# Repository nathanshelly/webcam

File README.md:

# Webcam

*Built by Jacob Bruce and Nathan Shelly*

## Description

This project aims to walk through the steps of designing and building a webcam from scratch. We'll walk through PCB (printed circuit board) design, soldering of components, 3D printing of the outer enclosure, MCU code and website code to enable you to make your own webcam, or modify our design however you'd like! This repository acts as the landng page to various parts of the project. Here we'll have various files such as our PCB designs, our CAD files and a bill of materials. Our [microcontroller code](https://github.com/nathanshelly/webcam_mcu_code) and [server code](https://github.com/nathanshelly/webcam_web_code) each have their own repositories, where our full code for each can be explored or downloaded. If you have any interest in duplicating or extending the project, please contact the authors - we'd be happy to help out in any way we can.

3D Printed Enclosure             |  Wood Milled Enclosure
:-------------------------:|:-------------------------:
  |  

## Assembly order

We recommend the following order to assemble this open-source project from scratch.

1. [Order components](#order-all-components)
2. [Solder board](#solder-components-onto-board)
3. [Configure wifi](#configure-wifi-chip)
4. [Configure MCU](#configure-microcontroller)
5. [Configure server](#configure-server)
6. [Print enclosure](#print-enclosure)

## Thanks

A big thank you to our instructor, Professor Ilya Mikhelson of Northwestern University. This webcam project was created as a part of his Engineering System Design sequence.

## Order components

We've included a [Bill of Materials](./BOM.txt) that details all of the components used in the project - primarily components to be soldered onto the board, but also some cabling to connect to it.

Here are some potential places to order from: [Mouser](http://www.mouser.com/), [Digikey](https://www.digikey.com/), [Robotshop](http://www.robotshop.com/).

You'll also need to order the PCB to solder the components onto. We've included our [raw EAGLE files](./board/), as well as a set of [Gerber files](./board/gerber_files.zip) that can be sent directly to the manufacturer.

## Solder board

If you have experience with surface mount soldering, this should be fairly straightforward. If you do not, we recommend practicing some before working with any expensive components. [This playlist](https://www.youtube.com/playlist?list=PL1ec5YBm_crySPZat6Y5e9hxfIUI7d97B) has many useful videos for this project, including several specifically on soldering.

We recommend the following soldering order to unit test each component before moving forward.

1. Power circuit: barrel jack, voltage regulator, power indicator LED, associated resistors and capacitors. Confirm that ground and power are not connected via continuity test. Plug in power cord and confirm that the power indicator lights up.

2. Microcontroller, PLL circuit, crystal oscillator, buttons, associated bypass capacitors, and header pins. After soldering the MCU, confirm each connection via continuity test to another via or pad, and confirm that no pins are connected to power or ground that shouldn't be. Connect the Atmel debugger, power the circuit, and confirm that the device signature can be read from Atmel Studio.

3. Wifi Chip, indicator LEDs, header pins, and associated bypass capacitors. Again, confirm each connection individually before proceeding. To confirm proper operation, perform step 4 to configure the chip.

4. Microphone and associated passive components.

5. Camera module and associated passive components. Be sure to solder the connector without the module inserted, and again confirm connections individually before proceeding.

## Configure wifi chip

The wifi chip requires a fair degree of configuration to work correctly. Zentri helpfully includes an OS to which commands are issued, and it's quite easy to work with their [command API](https://docs.zentri.com/zentrios/wz/3.3/cmd/commands). We recommend issuing these commands via a terminal emulator ([TeraTerm](https://ttssh2.osdn.jp/index.html.en) for windows or [CoolTerm](http://freeware.the-meiers.org/) for Mac) connected to the header pins for the UART communication via an FTDI cable. If you use the FTDI cable, make sure that the microcontroller will not be attempting to use the UART bus (either because no code has been loaded onto it or because it does not configure or use its UART module), or bus contention will result. These operations can also be performed by editing the MCU code and running commands, but that's much more difficult and harder to read/interpret feedback.

1. Connect to the chip. Confirm your connection by hitting Enter; the chip should respond with Ready.
2. If you're using a network which requires registration, obtain its mac address via the get wl m query, and register it to the network.
3. Connect the device to your network with the setup command. Once the command has been run, find the device's network on your computer. Connect to it, visit setup.com, and follow the prompts to connect to the desired network. Thereafter, the web console can be accessed from `http://zentrios-XYZ.local/`, where XYZ are the last 3 digits of your wifi chip's serial number.
4. Register with Zentri, and claim your device via the dms claim command.
5. Update the device's firmware with the OTA command.
6. Set the indicator GPIOs to indicate on the correct LEDs by running the following commands:

```
set sy i g wlan 20
set sy i g network 21
set sy i g softap 22
```

7. (Do this step only if you want to serve over HTTPS) Load TLS certificate onto the chip using its file uploader. Change its default TLS certificate to this file via the ne t a command.

8. Change the baud rate by setting the ua b variable for UART1. The default speed for UART1 is 115200, and our system is designed to run at 2.5Mbauds. You may want to turn the baud rate down in the MCU code to test operation before turning both up to this high speed - we haven't found a terminal emulator that can successfully interpret messages at this speed, and any issues can be difficult to debug.

## Configure microcontroller

To load our MCU code (found in [this separate repository](https://github.com/nathanshelly/webcam_mcu_code)) onto the microcontroller, first connect your Atmel debugger to the corresponding header pins and to your computer. Open our Atmel project, and connect to the debugger. Compile and load the code - it should run correctly now that the wifi chip is properly configured.

## Configure server

Our back-end stack consists of NGINX and Tornado on a Google Compute Engine instance. This could be hosted on any cloud provider or personal server. NGNIX directly handles requests for our static HTML, CSS and Javascript files while serving as a reverse proxy forwarding dynamic websocket requests to our Tornado server. We currently serve the website over HTTPS though this is not strictly necessary. If you plan to also serve over HTTPS our [NGINX configuration file](./nginx_config) would require only changing the server name in the port 80 and 443 blocks and then updating the ssl_certificate/key lines to point to your certificate. If you've never served over HTTPS before but would like to try we highly recommend getting a certificate from [LetsEncrypt](https://letsencrypt.org/) (they have great documentation and are free!).

If you want to serve over HTTP instead you'll need to move the location directives from the 443 block to the 80 block and remove the `return 301 https://$server_name$request_uri;` line which redirects all HTTP traffic to HTTPS. The ssl_certificate/key lines can also be removed.

The static files and our Tornado server file are all hosted in [this repository](https://github.com/nathanshelly/webcam_web_code) along with a more in-depth description of setting up the website.

## Print enclosure

For designing the enclosure we used an online program called [Onshape](https://www.onshape.com/). This provides a convenient way to edit CAD files with low overhead though it lacks some functionality from a fuller editor like Solidworks. View our [Onshape project here](https://cad.onshape.com/documents/ae298fb239b6988d4ccff146/w/2fbac33a8452420bf0238e8e/e/6b2309d9b32e628505d094b1).

We've also provided the raw files in two different formats. If you'd like to modify our design [here](./enclosure/editable) are .sldprt files. If you'd like to print our design as is [here](./enclosure/printable) are .stl files.

## Enjoy!

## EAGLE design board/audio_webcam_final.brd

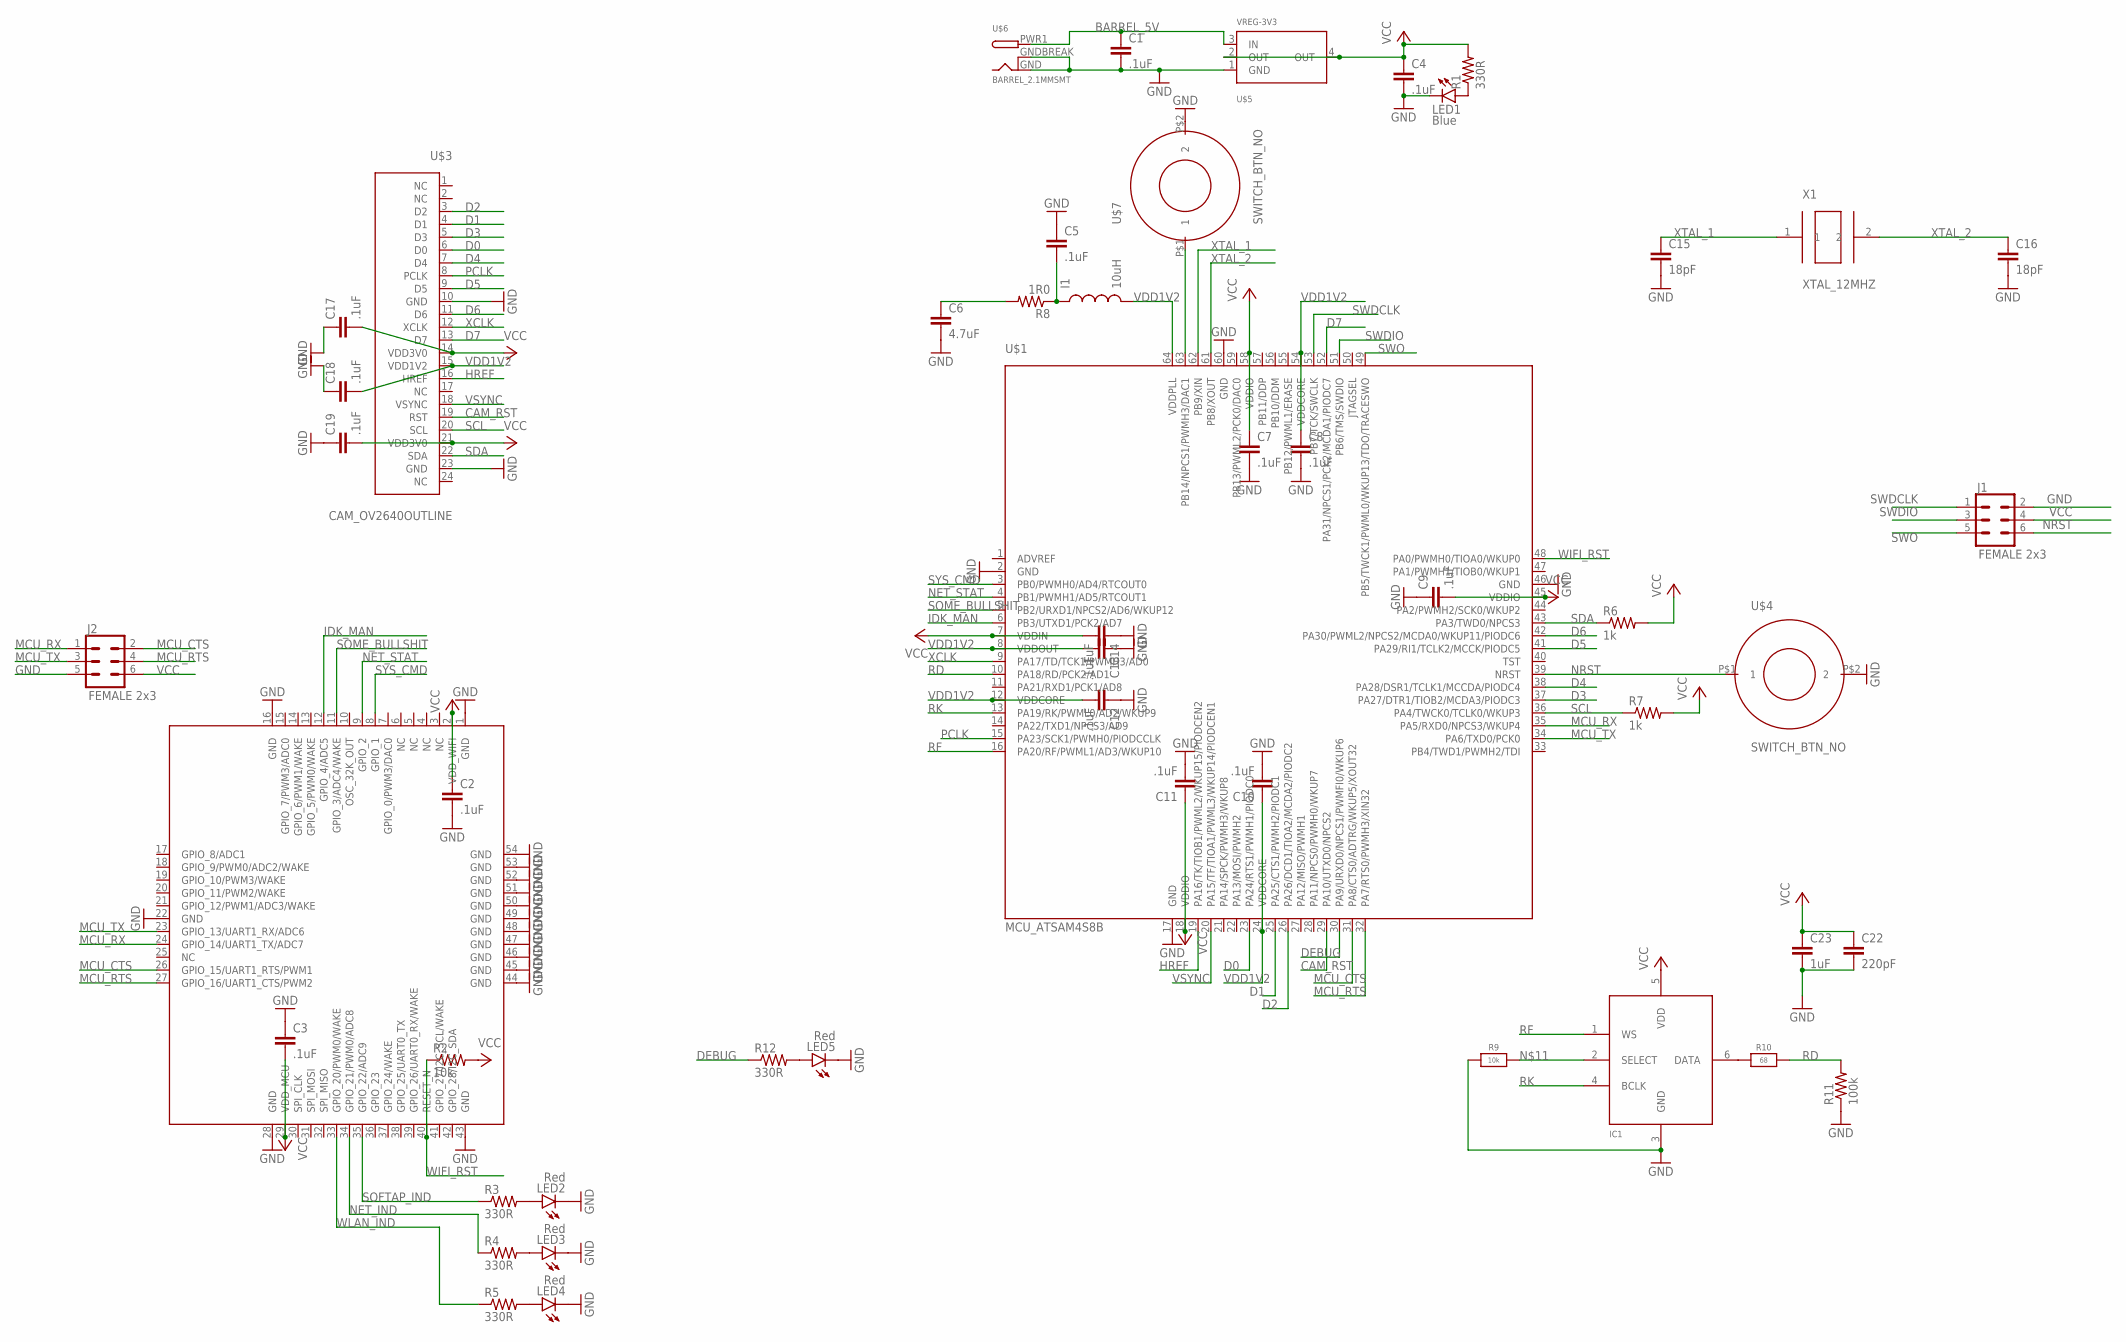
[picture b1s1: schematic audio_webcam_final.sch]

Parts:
C1, C2, C3, C4, C5, C7, C8, C9, C10, C11, C12, C13, C14, C17, C18, C19: .1uF; 0805
C6: 4.7uF; 0805
C15, C16: 18pF; 0805
C22: 220pF; 0805
C23: 1uF; 0805
I1: 10uH; 0805
IC1: MIC_I2S_SPH0645; SPH0645LM4H
J1, J2: FEMALE 2x3; 2X3
LED1: Blue; LED-0603
LED2, LED3, LED4, LED5: Red; LED-0603
R1, R3, R4, R5, R12: 330R; 0805
R2: 10k; 0805
R6, R7: 1k; 0805
R8: 1R0; 0805
R9: 10k; 0603-NO
R10: 68; 0603-NO
R11: 100k; 0805
U$1: MCU_ATSAM4S8B; QFP50P1200X1200X160-64N
U$2: WIFI_AMW004; AMW004
U$3: CAM_OV2640OUTLINE; CAM_CONN
U$4, U$7: SWITCH_BTN_NO; BTN_2
U$5: VREG-3V3; R-PDSO-G4_TI
U$6: BARREL_2.1MMSMT; DCJACK_2MM_SMT
X1: XTAL_12MHZ; ABM7-16.000MHZ-D2Y-T

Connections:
BARREL_5V: C1.1, U$5.3 (IN), U$6.PWR1 (PWR)
CAM_RST: U$1.29 (PA10/UTXD0/NPCS2), U$3.19 (RST)
D0: U$1.23 (PA24/RTS1/PWMH1/PIODC0), U$3.6 (D0)
D1: U$1.25 (PA25/CTS1/PWMH2/PIODC1), U$3.4 (D1)
D2: U$1.26 (PA26/DCD1/TIOA2/MCDA2/PIODC2), U$3.3 (D2)
D3: U$1.37 (PA27/DTR1/TIOB2/MCDA3/PIODC3), U$3.5 (D3)
D4: U$1.38 (PA28/DSR1/TCLK1/MCCDA/PIODC4), U$3.7 (D4)
D5: U$1.41 (PA29/RI1/TCLK2/MCCK/PIODC5), U$3.9 (D5)
D6: U$1.42 (PA30/PWML2/NPCS2/MCDA0/WKUP11/PIODC6), U$3.11 (D6)
D7: U$1.52 (PA31/NPCS1/PCK2/MCDA1/PIODC7), U$3.13 (D7)
DEBUG: R12.1, U$1.30 (PA9/URXD0/NPCS1/PWMFI0/WKUP6)
GND: C1.2, C2.2, C3.1, C4.2, C5.1, C6.2, C7.2, C8.2, C9.1, C10.2, C11.2, C12.1, C13.1, C14.1, C15.2, C16.2, C17.1, C18.1, C19.1, C22.2, C23.2, IC1.3 (GND), J1.2, J2.5, LED1.C, LED2.C, LED3.C, LED4.C, LED5.C, R9.1, R11.1, U$1.2 (GND), U$1.17 (GND), U$1.46 (GND), U$1.60 (GND), U$2.1 (GND), U$2.16 (GND), U$2.22 (GND), U$2.28 (GND), U$2.43 (GND), U$2.44 (GND), U$2.45 (GND), U$2.46 (GND), U$2.47 (GND), U$2.48 (GND), U$2.49 (GND), U$2.50 (GND), U$2.51 (GND), U$2.52 (GND), U$2.53 (GND), U$2.54 (GND), U$3.10 (GND), U$3.23 (GND), U$4.P$2 (2), U$5.1 (GND), U$6.GND, U$6.GNDBREAK, U$7.P$2 (2)
HREF: U$1.19 (PA16/TK/TIOB1/PWML2/WKUP15/PIODCEN2), U$3.16 (HREF)
IDK_MAN: U$1.6 (PB3/UTXD1/PCK2/AD7), U$2.12 (GPIO_4/ADC5)
MCU_CTS: J2.2, U$1.31 (PA8/CTS0/ADTRG/WKUP5/XOUT32), U$2.26 (GPIO_15/UART1_RTS/PWM1)
MCU_RTS: J2.4, U$1.32 (PA7/RTS0/PWMH3/XIN32), U$2.27 (GPIO_16/UART1_CTS/PWM2)
MCU_RX: J2.1, U$1.35 (PA5/RXD0/NPCS3/WKUP4), U$2.24 (GPIO_14/UART1_TX/ADC7)
MCU_TX: J2.3, U$1.34 (PA6/TXD0/PCK0), U$2.23 (GPIO_13/UART1_RX/ADC6)
unnamed: LED2.A, R3.2
unnamed: LED3.A, R4.2
unnamed: LED4.A, R5.2
unnamed: C5.2, I1.1, R8.1
unnamed: C6.1, R8.2
unnamed: LED1.A, R1.1
unnamed: U$1.63 (PB14/NPCS1/PWMH3/DAC1), U$7.P$1 (1)
unnamed: LED5.A, R12.2
unnamed: IC1.2 (SELECT), R9.2
unnamed: IC1.6 (DATA), R10.1
NET_IND: R4.1, U$2.34 (GPIO_21/PWM0/ADC8)
NET_STAT: U$1.4 (PB1/PWMH1/AD5/RTCOUT1), U$2.9 (GPIO_2)
NRST: J1.6, U$1.39 (NRST), U$4.P$1 (1)
PCLK: U$1.15 (PA23/SCK1/PWMH0/PIODCCLK), U$3.8 (PCLK)
RD: R10.2, R11.2, U$1.10 (PA18/RD/PCK2/AD1)
RF: IC1.1 (WS), U$1.16 (PA20/RF/PWML1/AD3/WKUP10)
RK: IC1.4 (BCLK), U$1.13 (PA19/RK/PWML0/AD2/WKUP9)
SCL: R7.1, U$1.36 (PA4/TWCK0/TCLK0/WKUP3), U$3.20 (SCL)
SDA: R6.1, U$1.43 (PA3/TWD0/NPCS3), U$3.22 (SDA)
SOFTAP_IND: R3.1, U$2.35 (GPIO_22/ADC9)
SOME_BULLSHIT: U$1.5 (PB2/URXD1/NPCS2/AD6/WKUP12), U$2.11 (GPIO_3/ADC4/WAKE)
SWDCLK: J1.1, U$1.53 (PB7/TCK/SWCLK)
SWDIO: J1.3, U$1.51 (PB6/TMS/SWDIO)
SWO: J1.5, U$1.49 (PB5/TWCK1/PWML0/WKUP13/TDO/TRACESWO)
SYS_CMD: U$1.3 (PB0/PWMH0/AD4/RTCOUT0), U$2.8 (GPIO_1)
VCC: C2.1, C3.2, C4.1, C7.1, C9.2, C11.1, C14.2, C17.2, C19.2, C22.1, C23.1, IC1.5 (VDD), J1.4, J2.6, R1.2, R2.2, R6.2, R7.2, U$1.7 (VDDIN), U$1.18 (VDDIO), U$1.45 (VDDIO), U$1.58 (VDDIO), U$2.2 (VDD_WIFI), U$2.29 (VDD_MCU), U$3.14 (VDD3V0), U$3.21 (VDD3V0), U$5.2 (OUT), U$5.4 (OUT)
VDD1V2: C8.1, C10.1, C12.2, C13.2, C18.2, I1.2, U$1.8 (VDDOUT), U$1.12 (VDDCORE), U$1.24 (VDDCORE), U$1.54 (VDDCORE), U$1.64 (VDDPLL), U$3.15 (VDD1V2)
VSYNC: U$1.20 (PA15/TF/TIOA1/PWML3/WKUP14/PIODCEN1), U$3.18 (VSYNC)
WIFI_RST: R2.1, U$1.48 (PA0/PWMH0/TIOA0/WKUP0), U$2.40 (RESET_N)
WLAN_IND: R5.1, U$2.33 (GPIO_20/PWM0/WAKE)
XCLK: U$1.9 (PA17/TD/TCK1/PWMH3/AD0), U$3.12 (XCLK)
XTAL_1: C15.1, U$1.62 (PB9/XIN), X1.1
XTAL_2: C16.1, U$1.61 (PB8/XOUT), X1.2

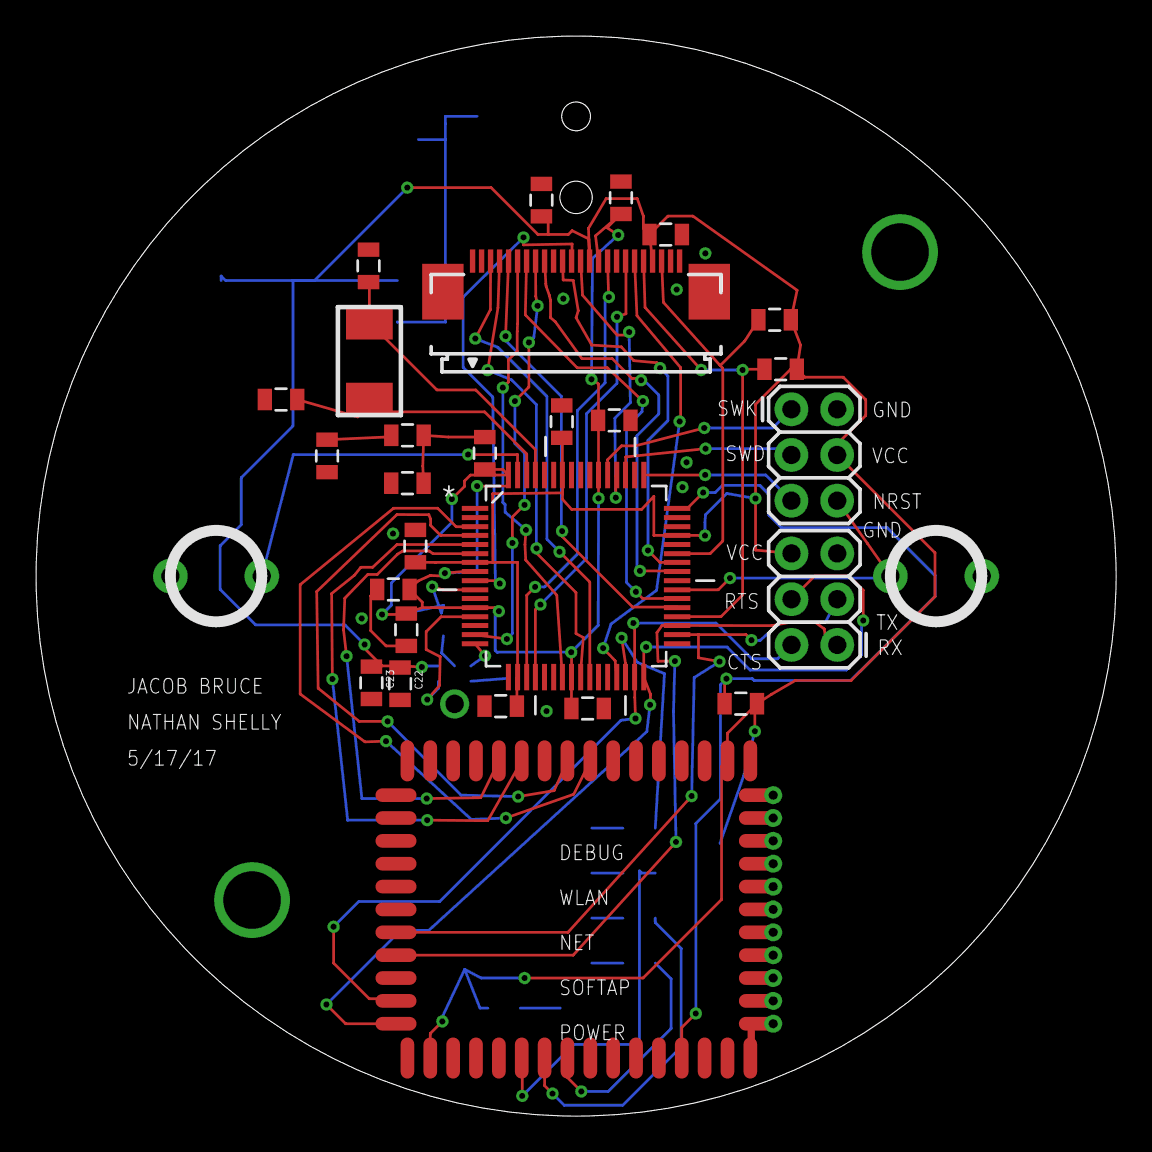
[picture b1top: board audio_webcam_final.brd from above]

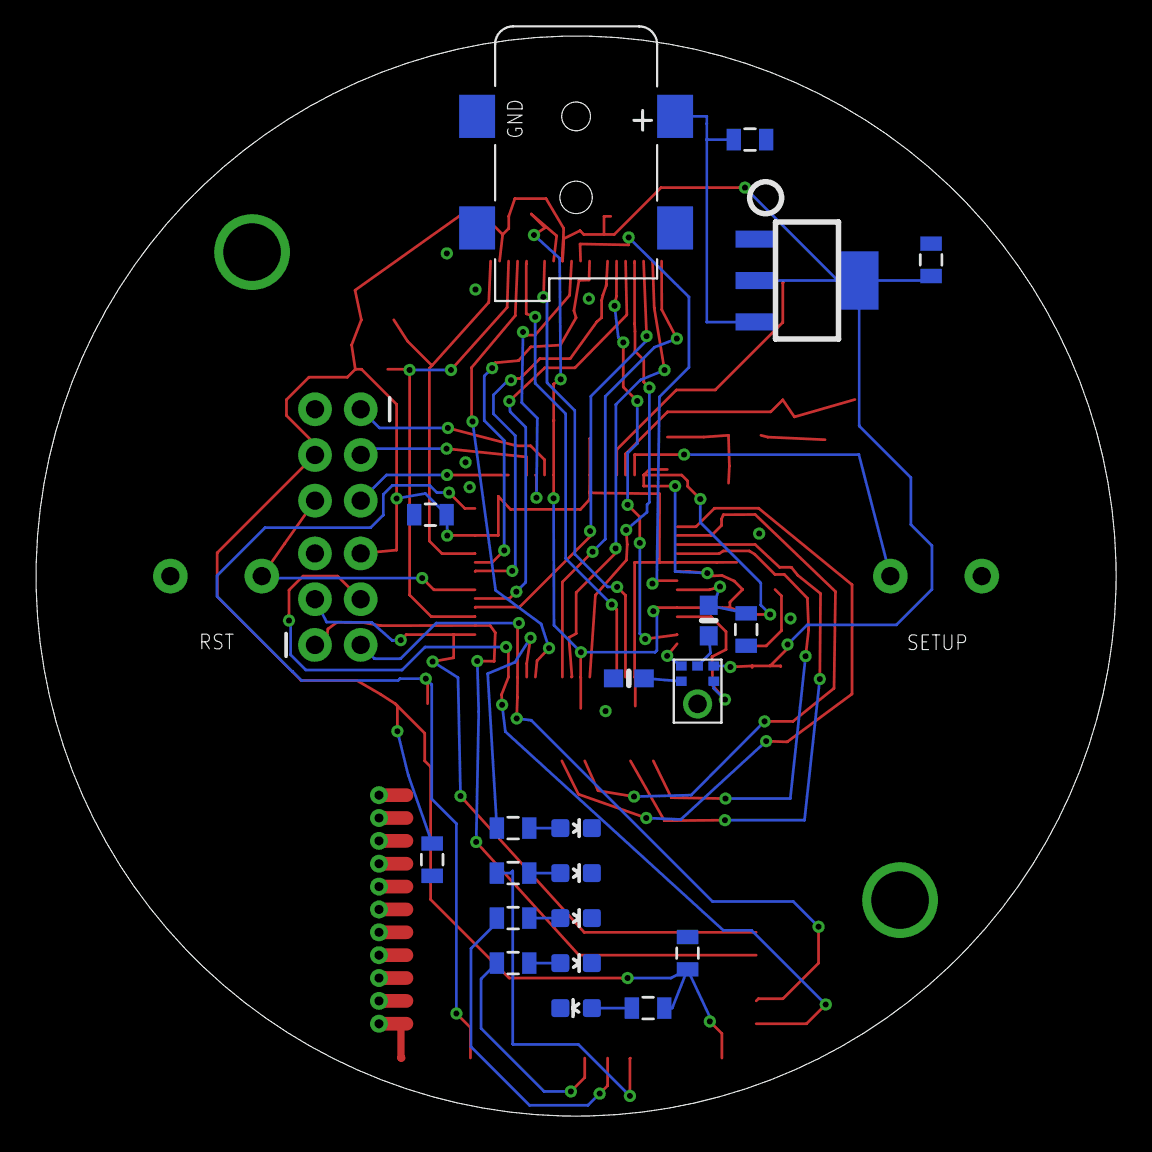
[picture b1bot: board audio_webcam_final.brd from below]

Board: 2 copper layers, 60.0 x 60.0 mm, 50 parts (21 on the bottom side), 51 nets.

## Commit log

2017-06-11 initial setup
2017-06-11 adding cad files, printable and editable
2017-06-11 adding webcam images
2017-06-11 minor change
2017-06-11 Added bill of materials
2017-06-11 Added some wifi instructions
2017-06-11 Link updates
2017-06-11 Markdown changes
2017-06-11 Wifi instructions complete
2017-06-11 added printing enclosure
2017-06-11 text for order all components section
2017-06-11 Microcontroller instructions
2017-06-11 added nginx configuration
2017-06-11 starting thoughts for configure server section
2017-06-11 Added PCB files
2017-06-11 Brief PCB order description
2017-06-12 added photos
2017-06-12 Table of contents
2017-06-12 testing side by side image placement
2017-06-12 better side by side image placement
2017-06-12 External and internal links
2017-06-12 Links fixed
2017-06-12 Bill of Materials
2017-06-12 removed unnecessary configuration lines
2017-06-12 fleshing out server configuration
2017-06-12 corrected links
2017-06-12 finishing up configure server section
2017-06-12 Parenthetical
2017-06-19 Updated BOM

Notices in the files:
parts and their libraries:
SparkFun-Connectors: Licensing: Creative Commons ShareAlike 4.0 International - https://creativecommons.org/licenses/by-sa/4.0
